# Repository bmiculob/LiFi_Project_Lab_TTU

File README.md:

# LiFi_Project_Lab_TTU
This a git repository containing source code as well as schematics for the Li-Fi project at Texas Tech.

Sponsored by Dr. Zhaoyang Fan
# System Operating Instructions.
1.	Adjust the transmitter and the receiver with the lens so that the light is focused on the photodiode on the receiver side.
	*	Transmitter LED is powered with 12 V
	*	Turn the transmitter microcontroller off so that the LED remains on when powered with 12 V
2.	Keep only one microcontroller plugged into the laptop whether it be the transmitter or receiver.
3.	Got the the command prompt and type the command "mode" to determine which COM port it is and write it down or memorize it.
4.	Do the same for the other microcontroller.
5.	Open both the transmitter and receiver UI.
6.	Configure the transmitter values so that the Serial Port and Baudrate (200000) are set. All other values should remain default.
7.	Configure the receiver values so that the Serial Port and Baudrate (230414) are set. All other values should remain default.
8.	Try the test signal and see that the receiver detects it.
	*	If the indicator doesn’t work then save the data to file and check it.
9.	For transmitting a file chose a file on the transmitter side by clicking the browse button.
10.	On the receiver side choose a file path to save by clicking the browse button.
	*	Every time the path is changed the UART connection must toggle from closed state to open state.
11.	Once both UI’s are configured click the transmit button on the transmitter side to transmit the file.
12.	Once it is verified that the receiver is done transmitting close the UART connection and check if the file transmitted successfully.
# Schematics
The jumpers are referenced from the chip side of the tiva microcontroller.
## Transmitter
![alt text][Transmitter]
## Receiver
![alt text][Receiver]

[Transmitter]: https://github.com/soukoba/LiFi_Project_Lab_TTU/blob/master/TransmitterSchematic.PNG
[Receiver]: https://github.com/soukoba/LiFi_Project_Lab_TTU/blob/master/ReceiverSchematic.PNG

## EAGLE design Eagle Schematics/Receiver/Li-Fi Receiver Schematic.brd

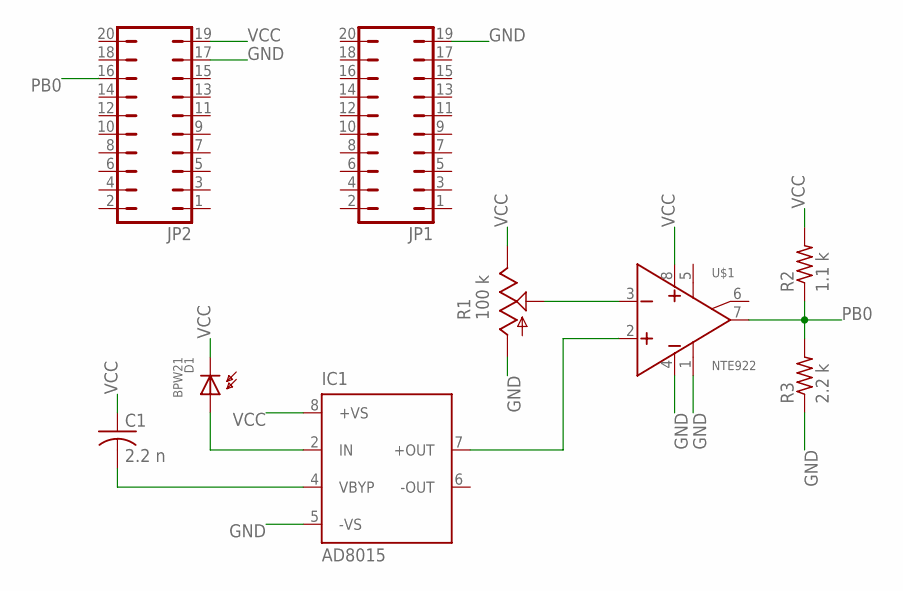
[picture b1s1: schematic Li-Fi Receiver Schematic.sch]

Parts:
C1: 2.2 n; C0805
D1: BPW21; TO-5
IC1: AD8015; SO8
JP1, JP2: JP10Q
R1: 100 k; B64Y
R2: 1.1 k; M0805
R3: 2.2 k; M0805
U$1: NTE922; DIP8

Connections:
GND: IC1.5 (-VS), JP1.19, JP2.17, R1.A, R3.1, U$1.1, U$1.4
unnamed: R1.S, U$1.3
unnamed: IC1.7 (+OUT), U$1.2
unnamed: D1.AN, IC1.2 (IN)
unnamed: C1.2, IC1.4 (VBYP)
PB0: JP2.16, R2.1, R3.2, U$1.7
VCC: C1.1, D1.CATH, IC1.8 (+VS), JP2.19, R1.E, R2.2, U$1.8

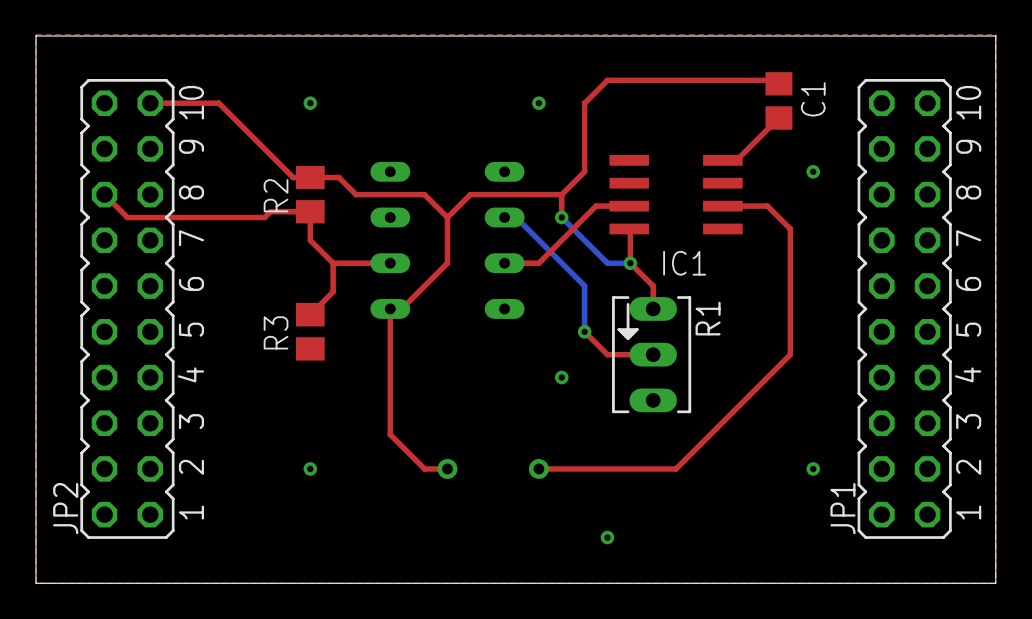
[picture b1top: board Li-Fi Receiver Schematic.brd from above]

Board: 2 copper layers, 53.3 x 30.4 mm, 9 parts (0 on the bottom side), 7 nets.

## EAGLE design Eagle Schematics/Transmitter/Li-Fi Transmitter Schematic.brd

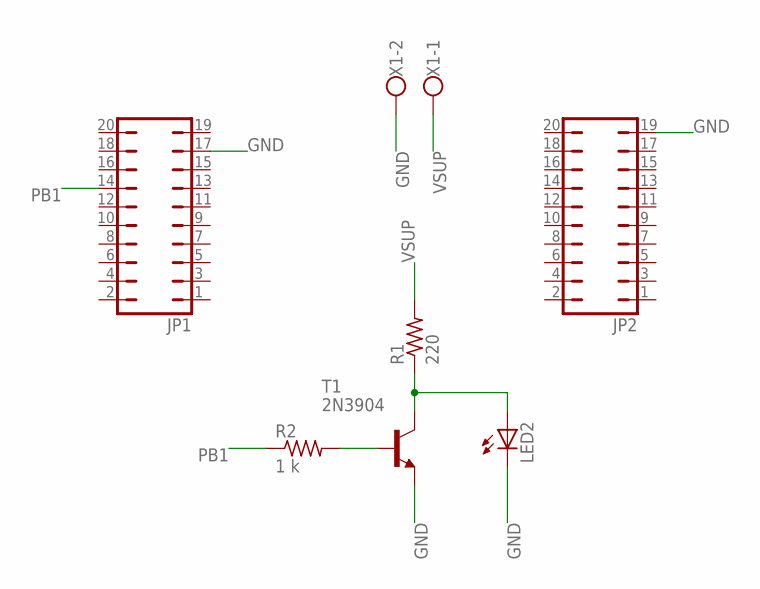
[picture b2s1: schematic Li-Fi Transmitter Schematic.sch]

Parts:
JP1, JP2: JP10Q
LED2: LEDKA-3528ASYC; KA-3528ASYC
R1: 220; R0805
R2: 1 k; R0805
T1: 2N3904; TO92
X1: W237-102

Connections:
GND: JP1.17, JP2.19, LED2.C, T1.3 (E), X1.2
unnamed: R2.2, T1.2 (B)
unnamed: LED2.A, R1.1, T1.1 (C)
PB1: JP1.14, R2.1
VSUP: R1.2, X1.1

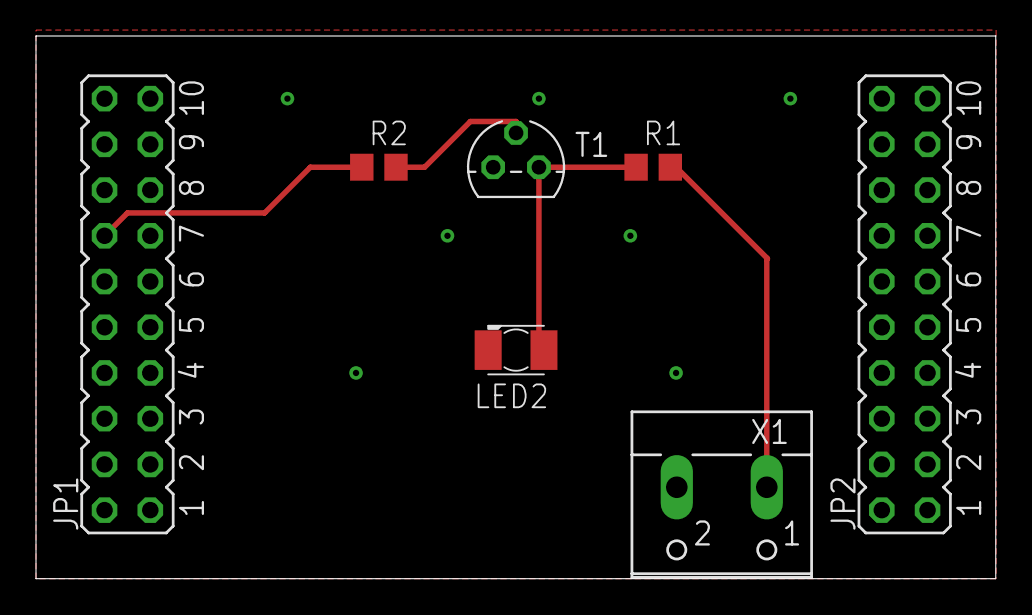
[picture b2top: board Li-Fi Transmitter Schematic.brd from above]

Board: 2 copper layers, 53.3 x 30.1 mm, 7 parts (0 on the bottom side), 5 nets.

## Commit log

2017-05-04 Initial Stuff
2017-05-04 Executables
2017-05-04 Tiva Source Code
2017-05-04 UI Changes
2017-05-05 "Changes to Receiver UI"
2017-05-05 Changes to Receiver UI
2017-05-10 UI Updates
2017-05-14 Updates UI and schematics
2017-05-14 Schematic Changes
2017-05-14 Readme Changes
2017-05-15 Lab Report
2017-05-17 Updated readme with instruction for hardware
2017-05-17 Updates to readme with system instructions
2017-05-17 Schematic Images
2017-05-17 Updates to readme
2017-05-17 Updates to readme with schematics and system instructions
2017-05-21 File Testing UI Merged
